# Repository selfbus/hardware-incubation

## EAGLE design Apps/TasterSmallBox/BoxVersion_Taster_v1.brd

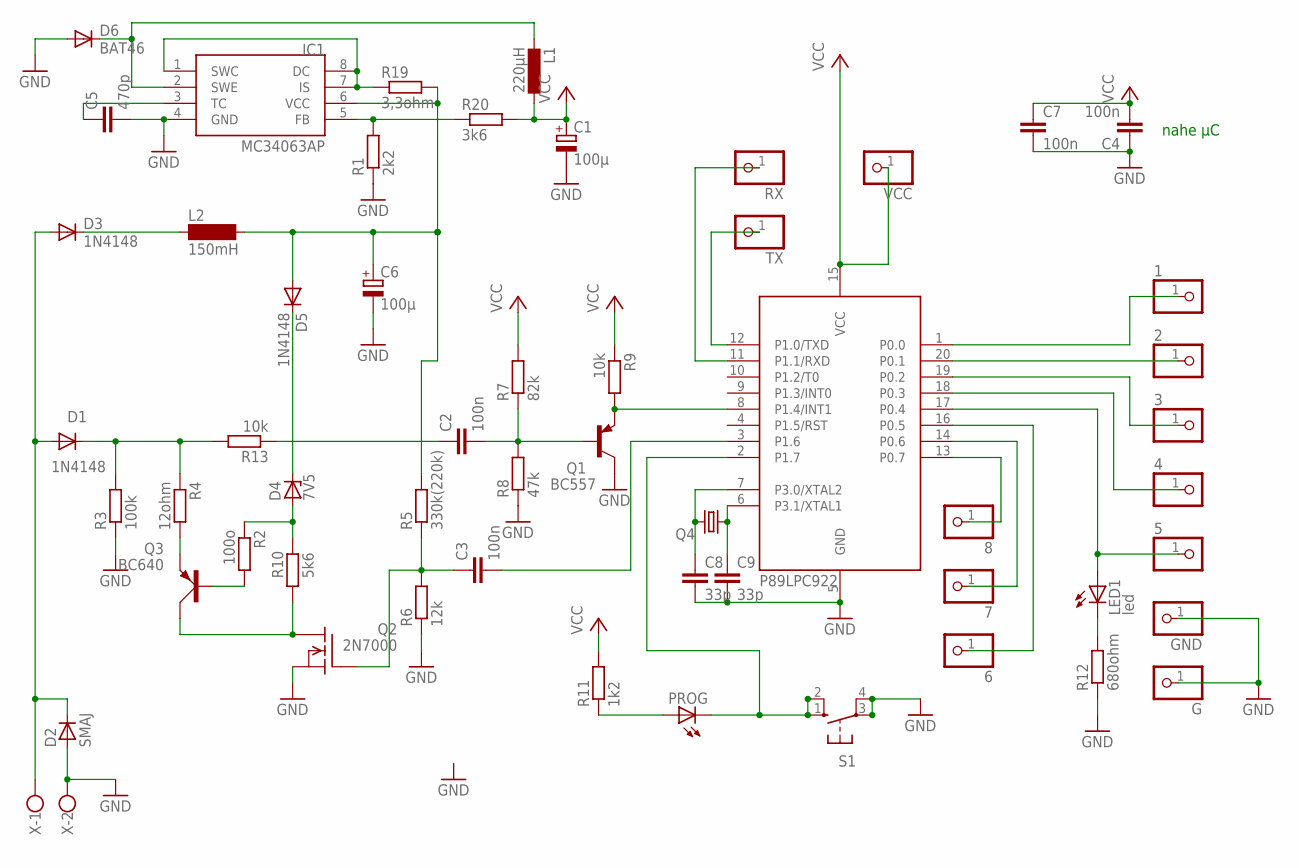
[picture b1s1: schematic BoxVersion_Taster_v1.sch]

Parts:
1, 2, 3, 4, 5, 6, 7, 8: PINHD-1X1; 1X01
C1: 100µ; E5-5
C2, C3, C4: 100n; C050-024X044
C5: 470p; C025-024X044
C6: 100µ; E5-6
C7: 100n; C1206
C8, C9: 33p; C1206
D1, D3, D5: 1N4148; D-2.5
D2: SMAJ; MELF-MLL41
D4: 7V5; ZDIO-2.5
D6: BAT46; D-2.5
G: PINHD-1X1; 1X01
GND: PINHD-1X1; 1X01
IC1: MC34063AP; DIL08
L1: 220µH; 0204/7
L2: 150mH; SD12K100
LED1: led; LZR181
PROG: LEDLZR181; LZR181
Q1: BC557; TO92
Q2: 2N7000; TO237
Q3: BC640; SOT54D
Q4: CRYSTALHC49S; HC49/S
R1: 2k2; 0207/2V
R2: 100o; 0207/2V
R3: 100k; 0207/2V
R4: 12ohm; 0207/2V
R5: 330k(220k); 0207/2V
R6: 12k; 0207/2V
R7: 82k; 0207/2V
R8: 47k; 0204/7
R9, R13: 10k; 0207/2V
R10: 5k6; 0207/2V
R11: 1k2; 0207/2V
R12: 680ohm; 0204/7
R19: 3,3ohm; 0207/2V
R20: 3k6; 0207/2V
RX: PINHD-1X1; 1X01
S1: 10-XX; B3F-10XX
TX: PINHD-1X1; 1X01
U1: 89LPC922; DIL20
VCC: PINHD-1X1; 1X01
X: W237-02P; W237-132

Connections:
GND: C1.-, C4.1, C5.2, C6.-, C7.2, C8.2, C9.2, D2.2 (A), D6.A, G.1, GND.1, IC1.4 (GND), Q1.3 (C), Q2.3 (S), R1.1, R3.1, R6.1, R8.1, R12.1, S1.3, S1.4 (P1), U1.5 (GND), X.2
unnamed: Q1.1 (E), R9.2, U1.8 (P1.4/INT1)
unnamed: C2.2, Q1.2 (B), R7.1, R8.2
unnamed: IC1.5 (FB), R1.2, R20.1
unnamed: IC1.1 (SWC), IC1.7 (IS), IC1.8 (DC), R19.1
unnamed: C3.2, U1.3 (P1.6)
unnamed: Q2.1 (D), Q3.C, R10.1
unnamed: C6.+, D5.A, IC1.6 (VCC), L2.2, R5.2, R19.2
unnamed: D3.C, L2.1
unnamed: D1.C, R3.2, R4.1, R13.2
unnamed: D6.C, IC1.2 (SWE), L1.2
unnamed: D4.A, R2.1, R10.2
unnamed: Q3.E, R4.2
unnamed: C5.1, IC1.3 (TC)
unnamed: Q3.B, R2.2
unnamed: 5.1, LED1.A, U1.17 (P0.4)
unnamed: D1.A, D2.1 (C), D3.A, X.1
unnamed: PROG.K (C), S1.1 (S), S1.2 (S1), U1.2 (P1.7)
unnamed: LED1.K (C), R12.2
unnamed: PROG.A, R11.1
unnamed: 3.1, U1.19 (P0.2)
unnamed: 1.1, U1.1 (P0.0)
unnamed: 2.1, U1.20 (P0.1)
unnamed: 4.1, U1.18 (P0.3)
unnamed: TX.1, U1.12 (P1.0/TXD)
unnamed: RX.1, U1.11 (P1.1/RXD)
unnamed: 6.1, U1.16 (P0.5)
unnamed: 8.1, U1.13 (P0.7)
unnamed: 7.1, U1.14 (P0.6)
unnamed: C9.1, Q4.1, U1.6 (P3.1/XTAL1)
unnamed: C8.1, Q4.2, U1.7 (P3.0/XTAL2)
unnamed: C2.1, R13.1
unnamed: C3.1, Q2.2 (G), R5.1, R6.2
unnamed: D4.C, D5.C
VCC: C1.+, C4.2, C7.1, L1.1, R7.2, R9.1, R11.2, R20.2, U1.15 (VCC), VCC.1

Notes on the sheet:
nahe µC
P89LPC922

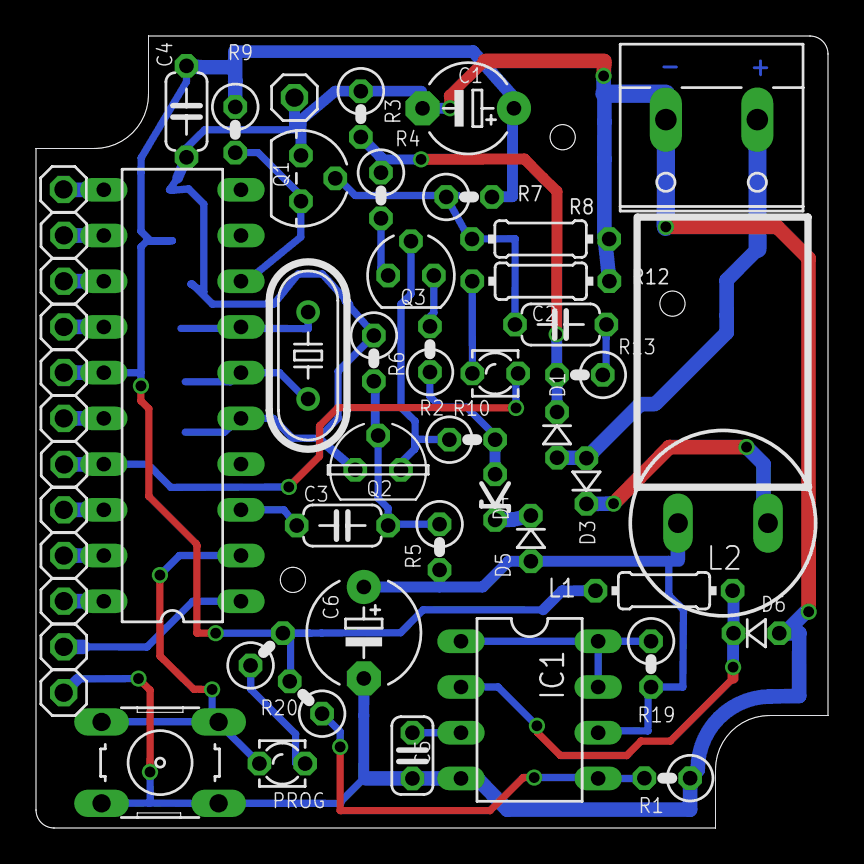
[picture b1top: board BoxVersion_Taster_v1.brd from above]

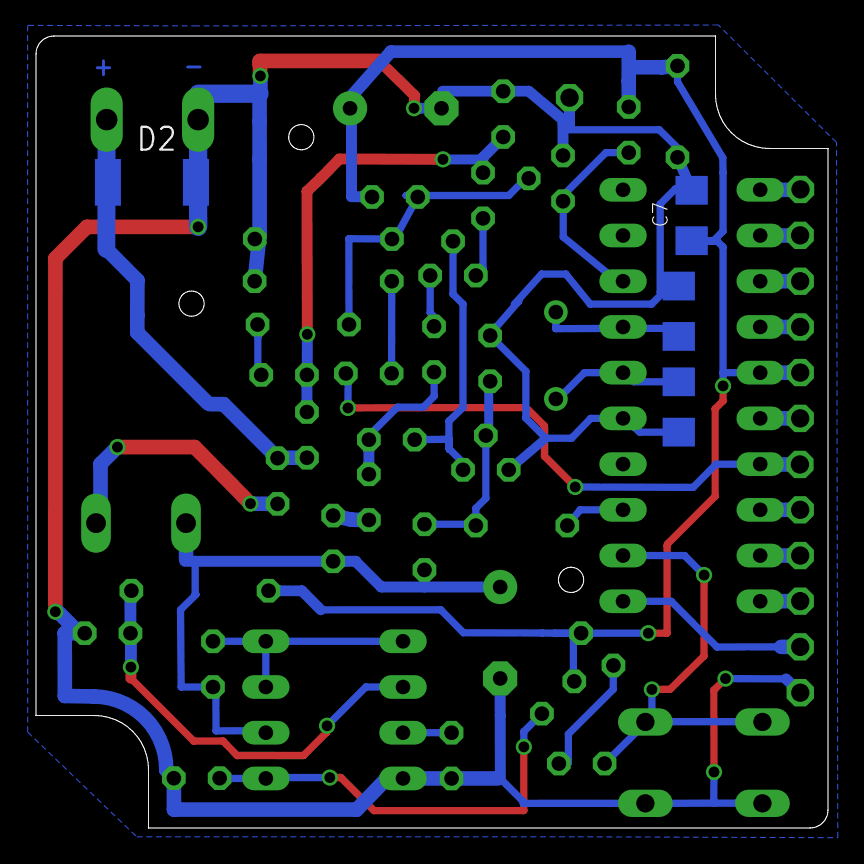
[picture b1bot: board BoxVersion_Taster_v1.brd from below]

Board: 2 copper layers, 44.0 x 44.0 mm, 56 parts (4 on the bottom side), 35 nets.

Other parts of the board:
U$1: 1551R

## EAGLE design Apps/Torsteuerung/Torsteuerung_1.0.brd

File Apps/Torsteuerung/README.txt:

Garagentor Steuerung
====================

Ziel: Ansteuerung eines Garagentor Antriebs über EIB.

Die Idee ist einen Freebus LPC Controller mit einer 8in Applikationsplatine
zu verwenden. Die Applikationsplatine wird so adaptiert dass zwei der
Eingänge als Ausgänge verwendet werden. 

Eingänge
--------

2 Endschalter Tor offen / zu
2 Motorstrom Indikatoren öffnet / schließt
1 Licht (blinkt bei Fehler)

Ausgänge
--------

Zwei Modi: entweder mit einem Ausgang alle 4 Zustände durchschalten
(Auf, Stopp, Zu, Stopp) oder mit zwei Ausgängen auf und zu ansteuern.

1 Tor auf / Tor unversal
1 Tor zu

Com Objekte
-----------

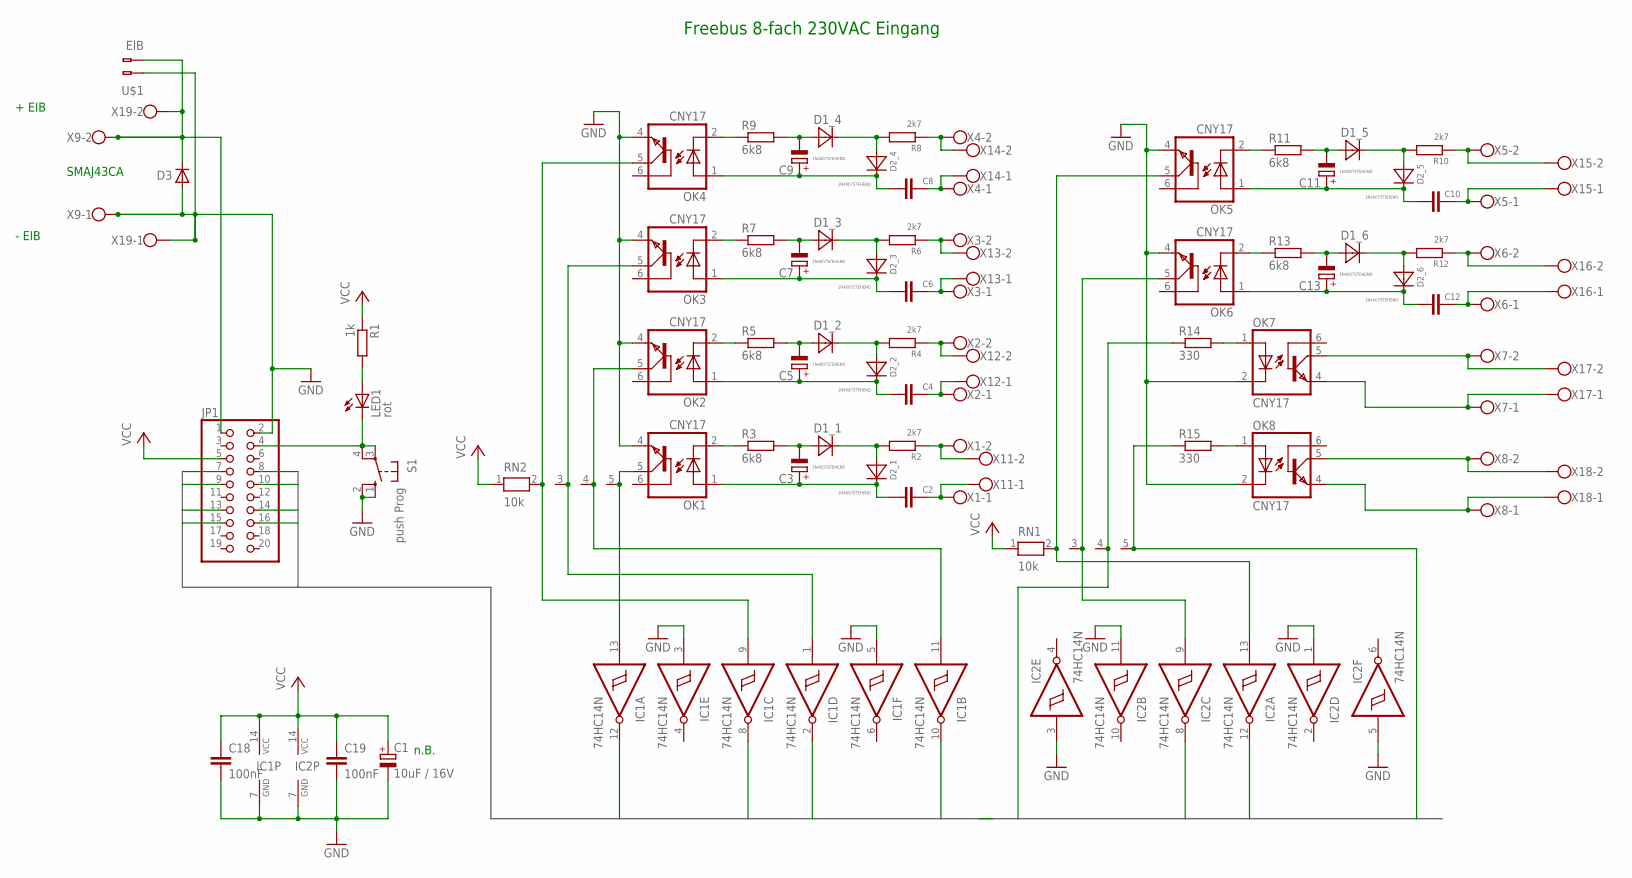
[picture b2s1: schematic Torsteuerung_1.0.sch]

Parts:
C1: 10uF / 16V; E2-4
C2, C4, C6, C8, C10, C12: C-EU075-063X106; C075-063X106
C3, C5, C7, C9, C11, C13: CPOL-EUE2-4; E2-4
C18, C19: 100nF; C050-024X044
D1_1, D1_2, D1_3, D1_4, D1_5, D1_6, D2_1, D2_2, D2_3, D2_4, D2_5, D2_6: 1N4007STEHEND; RAD2,5
D3: D-SMB; SMB
IC1, IC2: 74HC14N; DIL14
JP1: PINHD-2X10; 2X10
LED1: rot; LED3MM
OK1, OK2, OK3, OK4, OK5, OK6, OK7, OK8: CNY17; DIL06
R1: 1k; 0204/7
R2, R4, R6, R8, R10, R12: 2k7; 0207/2V
R3, R5, R7, R9, R11, R13: 6k8; 0207/2V
R14, R15: 330; 0204/5
RN1, RN2: 10k; RN-5
S1: push Prog; B3F-10XX
U$1: EIB; BUSKLEMME243-724
X1, X2, X3, X4, X5, X6, X7, X8, X9: W237-102
X11, X12, X13, X14, X15, X16, X17, X18, X19: W237-102AKL007-2P; AKL007-02

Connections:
230+_1: C2.1, C3.+, D2_1.C, OK1.1 (A)
230+_2: C4.1, C5.+, D2_2.C, OK2.1 (A)
230+_3: C6.1, C7.+, D2_3.C, OK3.1 (A)
230+_4: C8.1, C9.+, D2_4.C, OK4.1 (A)
230+_5: C10.1, C11.+, D2_5.C, OK5.1 (A)
230+_6: C12.1, C13.+, D2_6.C, OK6.1 (A)
230-_1: C3.-, D1_1.A, R3.2
230-_2: C5.-, D1_2.A, R5.2
230-_3: C7.-, D1_3.A, R7.2
230-_4: C9.-, D1_4.A, R9.2
230-_5: C11.-, D1_5.A, R11.2
230-_6: C13.-, D1_6.A, R13.2
230N_1: D1_1.C, D2_1.A, R2.2
230N_2: D1_2.C, D2_2.A, R4.2
230N_3: D1_3.C, D2_3.A, R6.2
230N_4: D1_4.C, D2_4.A, R8.2
230N_5: D1_5.C, D2_5.A, R10.2
230N_6: D1_6.C, D2_6.A, R12.2
GND: C1.-, C18.2, C19.2, D3.2 (A), IC1.3 (I), IC1.5 (I), IC1.7 (GND), IC2.1 (I), IC2.3 (I), IC2.5 (I), IC2.7 (GND), IC2.11 (I), JP1.2, OK1.4 (EMI), OK2.4 (EMI), OK3.4 (EMI), OK4.4 (EMI), OK5.4 (EMI), OK6.4 (EMI), OK7.2 (C), OK8.2 (C), S1.1 (S), S1.2 (S1), U$1.1 (B-1), X9.1, X19.1
IO1: IC1.12 (O), JP1.7
IO2: IC1.10 (O), JP1.8
IO3: IC1.2 (O), JP1.9
IO4: IC1.8 (O), JP1.10
IO5: IC2.12 (O), JP1.13
IO6: IC2.8 (O), JP1.14
IO7: JP1.15, R14.1, RN1.4
IO8: JP1.16, R15.1, RN1.5
unnamed: C8.2, X4.1, X14.1
unnamed: R8.1, X4.2, X14.2
unnamed: C6.2, X3.1, X13.1
unnamed: R6.1, X3.2, X13.2
unnamed: C4.2, X2.1, X12.1
unnamed: R4.1, X2.2, X12.2
unnamed: C2.2, X1.1, X11.1
unnamed: R2.1, X1.2, X11.2
unnamed: R12.1, X6.2, X16.2
unnamed: C12.2, X6.1, X16.1
unnamed: OK7.5 (COL), X7.2, X17.2
unnamed: OK8.4 (EMI), X8.1, X18.1
unnamed: R10.1, X5.2, X15.2
unnamed: C10.2, X5.1, X15.1
unnamed: OK7.4 (EMI), X7.1, X17.1
unnamed: OK8.5 (COL), X8.2, X18.2
unnamed: IC2.13 (I), OK5.5 (COL), RN1.2
unnamed: IC2.9 (I), OK6.5 (COL), RN1.3
unnamed: D3.1 (C), JP1.1, U$1.2 (B-2), X9.2, X19.2
unnamed: OK8.1 (A), R15.2
unnamed: OK7.1 (A), R14.2
unnamed: IC1.13 (I), OK1.5 (COL), RN2.5
unnamed: IC1.11 (I), OK2.5 (COL), RN2.4
unnamed: JP1.4, LED1.K (C), S1.3, S1.4 (P1)
unnamed: LED1.A, R1.2
unnamed: IC1.1 (I), OK3.5 (COL), RN2.3
unnamed: IC1.9 (I), OK4.5 (COL), RN2.2
OPT_1: OK1.2 (C), R3.1
OPT_2: OK2.2 (C), R5.1
OPT_3: OK3.2 (C), R7.1
OPT_4: OK4.2 (C), R9.1
OPT_5: OK5.2 (C), R11.1
OPT_6: OK6.2 (C), R13.1
VCC: C1.+, C18.1, C19.1, IC1.14 (VCC), IC2.14 (VCC), JP1.5, R1.1, RN1.1, RN2.1

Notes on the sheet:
+ EIB
- EIB
Freebus 8-fach 230VAC Eingang
SMAJ43CA
n.B.

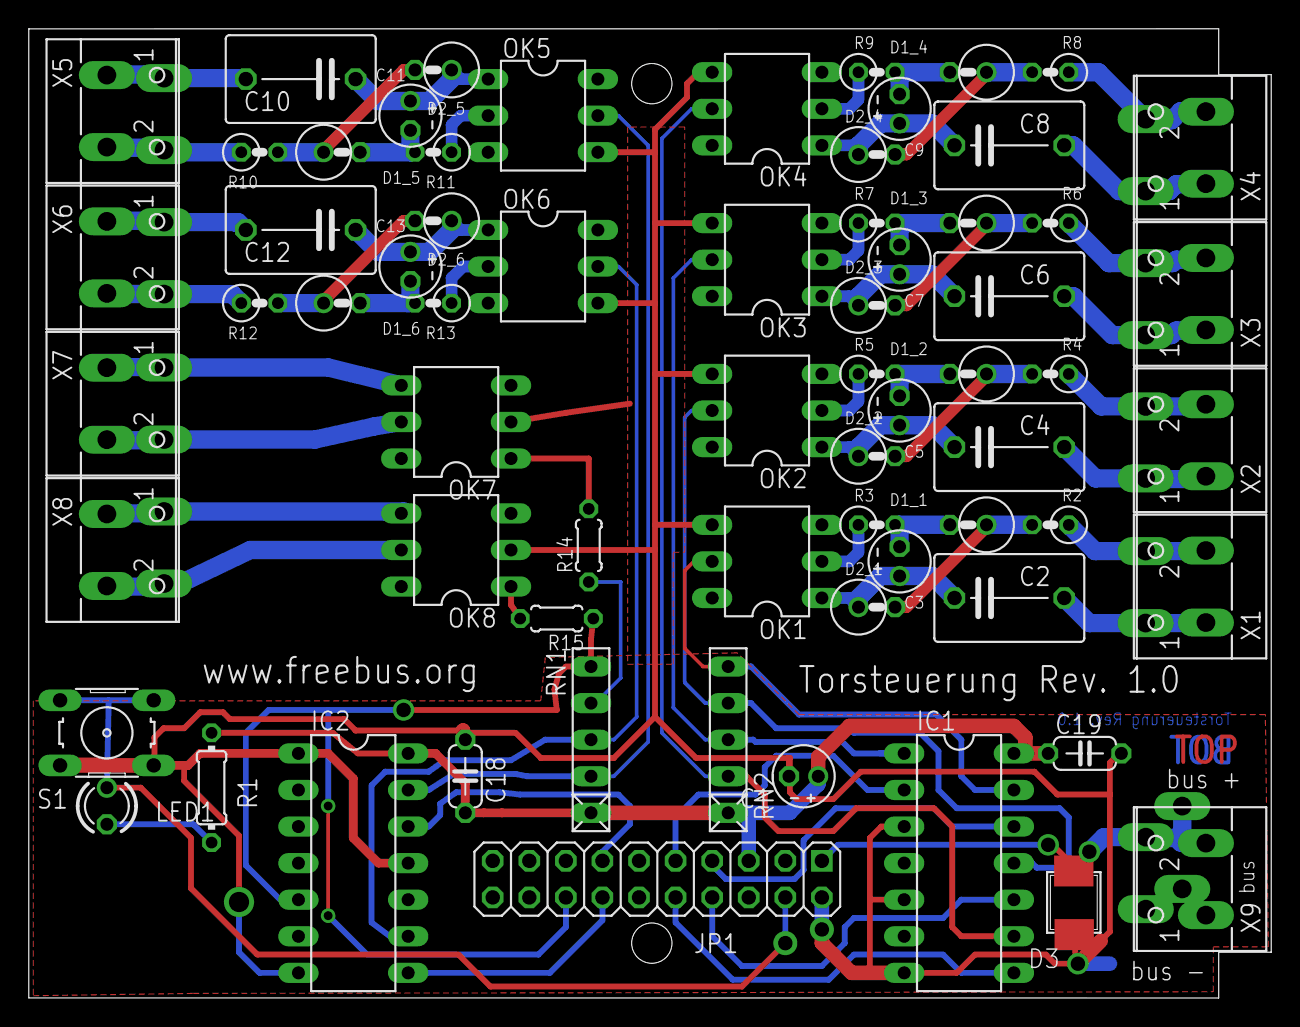
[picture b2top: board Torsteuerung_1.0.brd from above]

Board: 2 copper layers, 86.3 x 67.3 mm, 77 parts (0 on the bottom side), 61 nets.

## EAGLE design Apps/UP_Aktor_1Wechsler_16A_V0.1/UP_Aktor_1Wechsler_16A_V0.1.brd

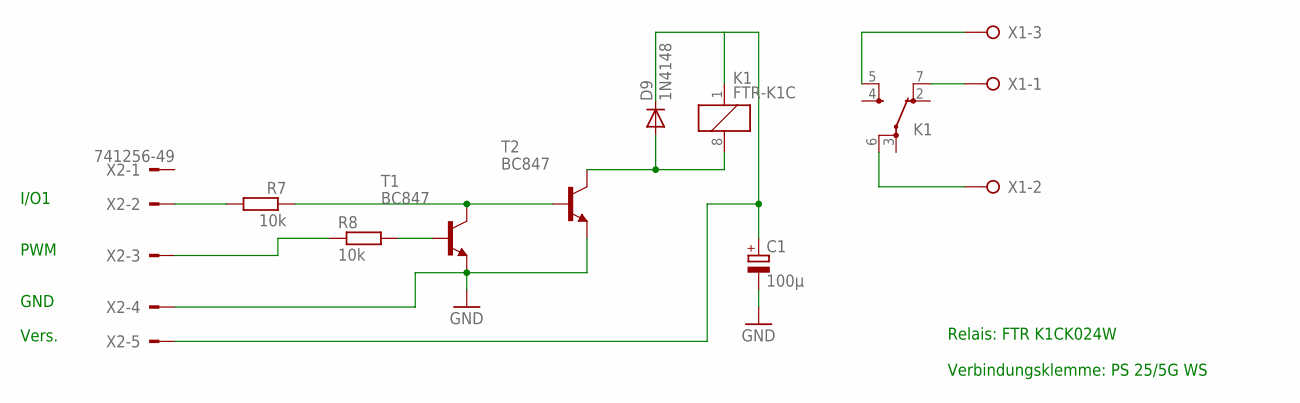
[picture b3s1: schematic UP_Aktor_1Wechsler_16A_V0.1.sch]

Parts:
C1: 100µ; E3,5-8
D9: 1N4148; MINIMELF
K1: FTR-K1C
R7, R8: 10k; M1206
T1, T2: BC847; SOT23
X1: W237-03P; W237-133
X2: 741256-49

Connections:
GND: C1.-, T1.2 (E), T2.2 (E), X2.4
IO2: R7.2, X2.2
unnamed: K1.5 (SB), X1.3
unnamed: K1.7 (OB), X1.1
unnamed: K1.6 (PB), X1.2
unnamed: R8.1, X2.3
unnamed: R7.1, T1.3 (C), T2.1 (B)
unnamed: R8.2, T1.1 (B)
R3: D9.A, K1.8 (2), T2.3 (C)
VDD_IN: C1.+, D9.C, K1.1, X2.5

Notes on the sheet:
PWM
I/O1
Vers.
GND
Relais: FTR K1CK024W Verbindungsklemme: PS 25/5G WS

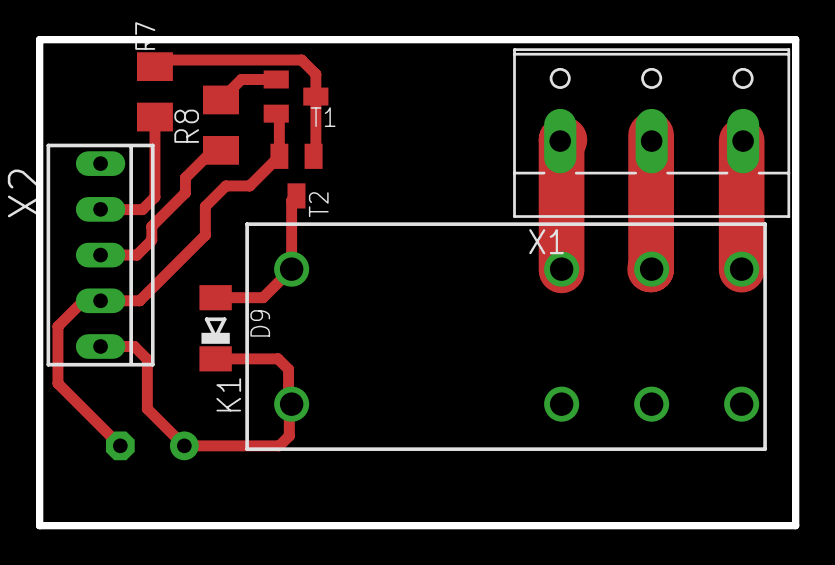
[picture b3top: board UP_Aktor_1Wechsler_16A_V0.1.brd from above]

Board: 2 copper layers, 42.0 x 27.0 mm, 9 parts (1 on the bottom side), 10 nets.

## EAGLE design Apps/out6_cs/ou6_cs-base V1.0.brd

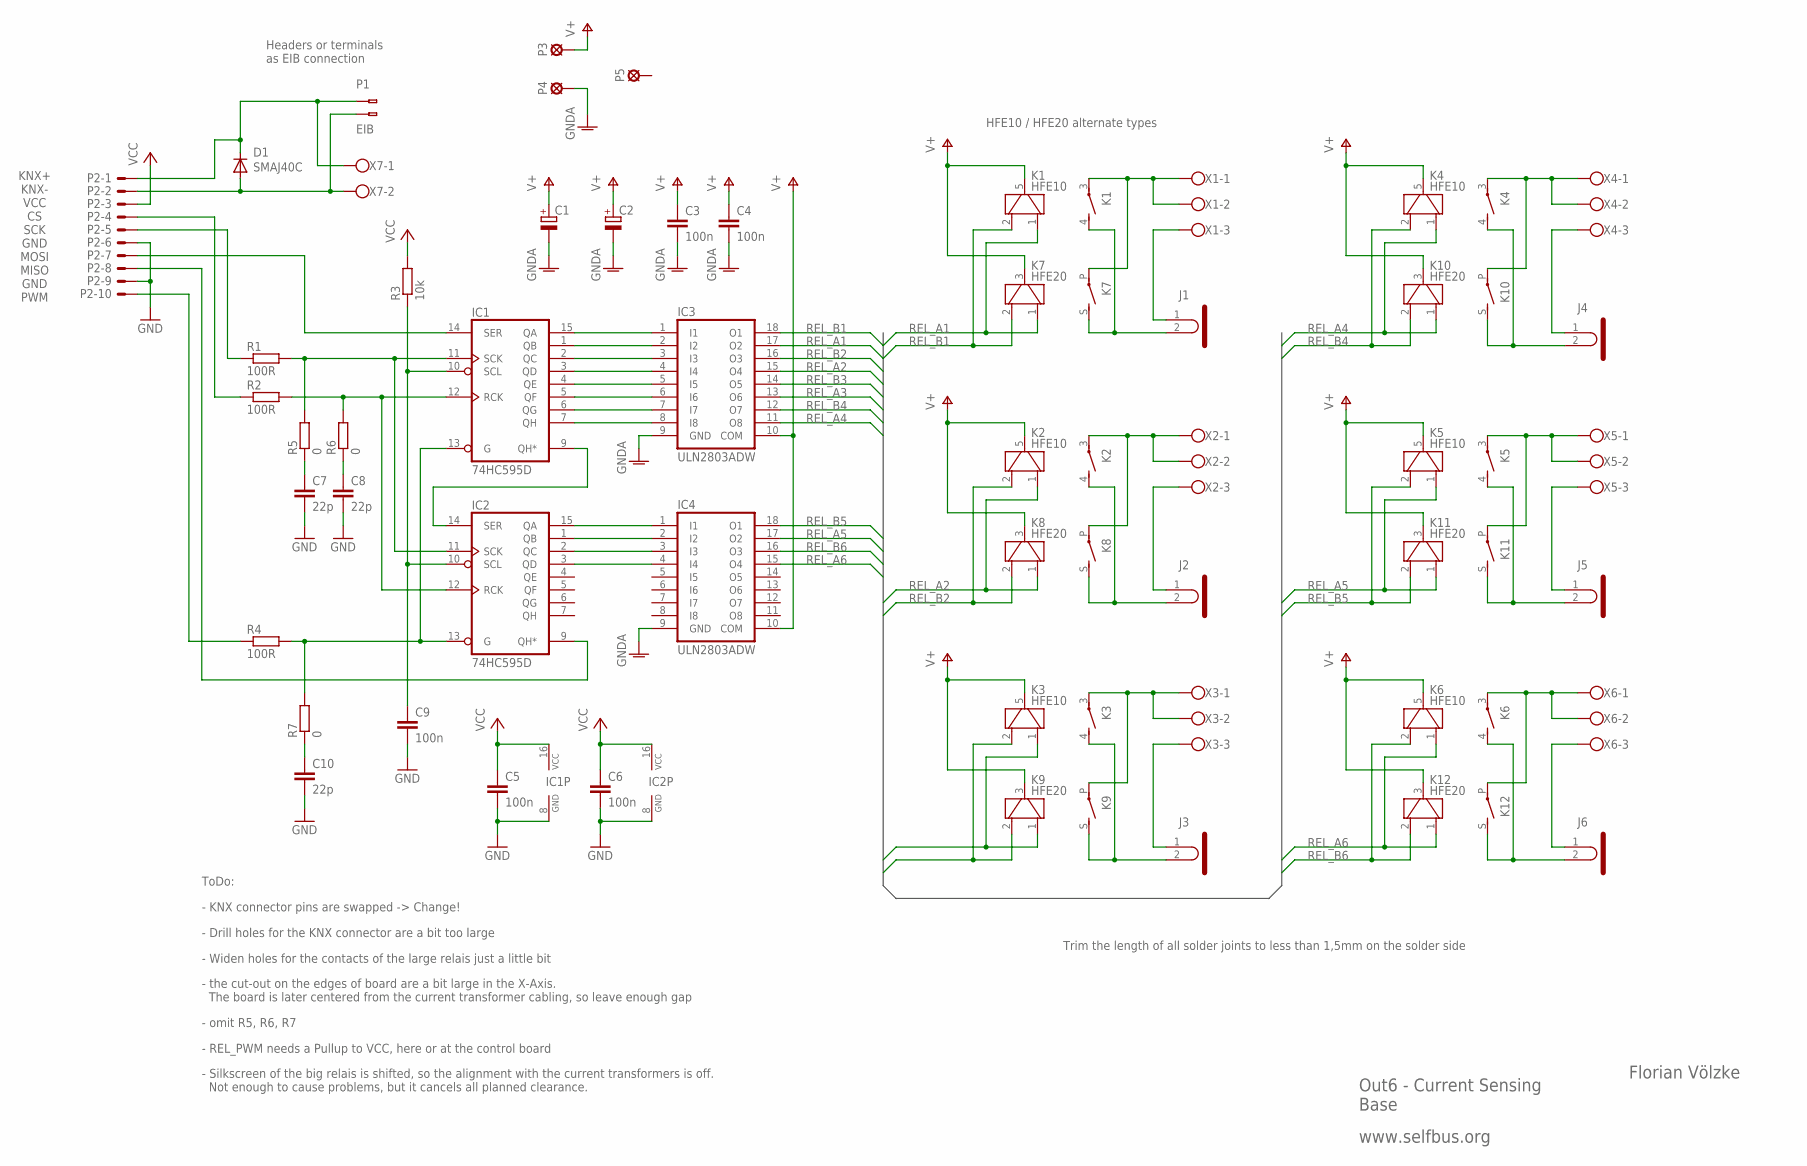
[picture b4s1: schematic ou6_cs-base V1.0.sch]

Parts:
C1: CPOL-EUE5-13-20; E5-13-20
C2: CPOL-EUE5-13-20R; E5-13-20R
C3, C4, C5, C6, C9: 100n; R0805M
C7, C8, C10: 22p; R0805M
D1: SMAJ40C; SMB
IC1, IC2: 74HC595D; SO16
IC3, IC4: ULN2803ADW; SO18W
J1, J2, J3, J4, J5, J6: IXFORMER_PRIMONLY; IXFORMERANTIPART
K1, K2, K3, K4, K5, K6: HFE10; PCB_REL_BIG_POWER_NO
K7, K8, K9, K10, K11, K12: HFE20; PCB_REL_HP_NO_SNGLPIN
P1: EIB; BUSKLEMME243-724
P2: ML10E; ML10
P3, P4, P5: SE1.5; SE15
R1, R2, R4: 100R; R0805M
R3: 10k; R0805M
R5, R6, R7: 0; R0805M
X1, X2, X3, X4, X5, X6: KLEMME3POL5_08
X7: KLEMME2POL5_08

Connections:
GND: C5.2, C6.2, C7.2, C8.2, C9.2, C10.2, IC1.8 (GND), IC2.8 (GND), P2.6, P2.9
GNDA: C1.-, C2.-, C3.2, C4.2, IC3.9 (GND), IC4.9 (GND), P4.MP
unnamed: IC1.9 (QH*), IC2.14 (SER)
unnamed: IC1.11 (SCK), IC2.11 (SCK), R1.2, R5.2
unnamed: IC1.12 (RCK), IC2.12 (RCK), R2.2, R6.2
unnamed: IC1.14 (SER), P2.7
unnamed: IC1.13 (G), IC2.13 (G), R4.2, R7.2
unnamed: K2.3, K8.P, X2.P$1, X2.P$2
unnamed: J3.2, K3.4 (S), K9.S
unnamed: J2.2, K2.4 (S), K8.S
unnamed: J1.2, K1.4 (S), K7.S
unnamed: J2.1, X2.P$3
unnamed: J1.1, X1.P$3
unnamed: K1.3, K7.P, X1.P$1, X1.P$2
unnamed: IC2.9 (QH*), P2.8
unnamed: K3.3, K9.P, X3.P$1, X3.P$2
unnamed: K4.3, K10.P, X4.P$1, X4.P$2
unnamed: J3.1, X3.P$3
unnamed: IC1.15 (QA), IC3.1 (I1)
unnamed: K5.3, K11.P, X5.P$1, X5.P$2
unnamed: IC1.1 (QB), IC3.2 (I2)
unnamed: K6.3, K12.P, X6.P$1, X6.P$2
unnamed: IC1.2 (QC), IC3.3 (I3)
unnamed: J6.1, X6.P$3
unnamed: J6.2, K6.4 (S), K12.S
unnamed: J5.2, K5.4 (S), K11.S
unnamed: J4.2, K4.4 (S), K10.S
unnamed: IC1.3 (QD), IC3.4 (I4)
unnamed: IC1.4 (QE), IC3.5 (I5)
unnamed: IC1.5 (QF), IC3.6 (I6)
unnamed: IC1.6 (QG), IC3.7 (I7)
unnamed: J5.1, X5.P$3
unnamed: IC1.7 (QH), IC3.8 (I8)
unnamed: IC2.15 (QA), IC4.1 (I1)
unnamed: J4.1, X4.P$3
unnamed: IC2.1 (QB), IC4.2 (I2)
unnamed: IC2.2 (QC), IC4.3 (I3)
unnamed: IC2.3 (QD), IC4.4 (I4)
unnamed: C9.1, IC1.10 (SCL), IC2.10 (SCL), R3.1
unnamed: P2.5, R1.1
unnamed: P2.4, R2.1
unnamed: D1.1 (C), P1.1 (B-1), P2.1, X7.P$1
unnamed: P2.10, R4.1
unnamed: D1.2 (A), P1.2 (B-2), P2.2, X7.P$2
unnamed: C7.1, R5.1
unnamed: C8.1, R6.1
unnamed: C10.1, R7.1
REL_A1: IC3.17 (O2), K1.1 (3), K7.1 (3)
REL_A2: IC3.15 (O4), K2.1 (3), K8.1 (3)
REL_A3: IC3.13 (O6), K3.1 (3), K9.1 (3)
REL_A4: IC3.11 (O8), K4.1 (3), K10.1 (3)
REL_A5: IC4.17 (O2), K5.1 (3), K11.1 (3)
REL_A6: IC4.15 (O4), K6.1 (3), K12.1 (3)
REL_B1: IC3.18 (O1), K1.2, K7.2
REL_B2: IC3.16 (O3), K2.2, K8.2
REL_B3: IC3.14 (O5), K3.2, K9.2
REL_B4: IC3.12 (O7), K4.2, K10.2
REL_B5: IC4.18 (O1), K5.2, K11.2
REL_B6: IC4.16 (O3), K6.2, K12.2
V+: C1.+, C2.+, C3.1, C4.1, IC3.10 (COM), IC4.10 (COM), K1.5 (1), K2.5 (1), K3.5 (1), K4.5 (1), K5.5 (1), K6.5 (1), K7.3 (1), K8.3 (1), K9.3 (1), K10.3 (1), K11.3 (1), K12.3 (1), P3.MP
VCC: C5.1, C6.1, IC1.16 (VCC), IC2.16 (VCC), P2.3, R3.2

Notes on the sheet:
KNX+ KNX- VCC CS SCK GND MOSI MISO GND PWM
Florian Völzke
Out6 - Current Sensing Base
www.selfbus.org
HFE10 / HFE20 alternate types
Headers or terminals as EIB connection
ToDo:
- KNX connector pins are swapped -> Change!
- Drill holes for the KNX connector are a bit too large
- Widen holes for the contacts of the large relais just a little bit
Trim the length of all solder joints to less than 1,5mm on the solder side
- the cut-out on the edges of board are a bit large in the X-Axis. The board is later centered from the current transformer cabling, so leave enough gap
- omit R5, R6, R7
- REL_PWM needs a Pullup to VCC, here or at the control board
- Silkscreen of the big relais is shifted, so the alignment with the current transformers is off. Not enough to cause problems, but it cancels all planned clearance.

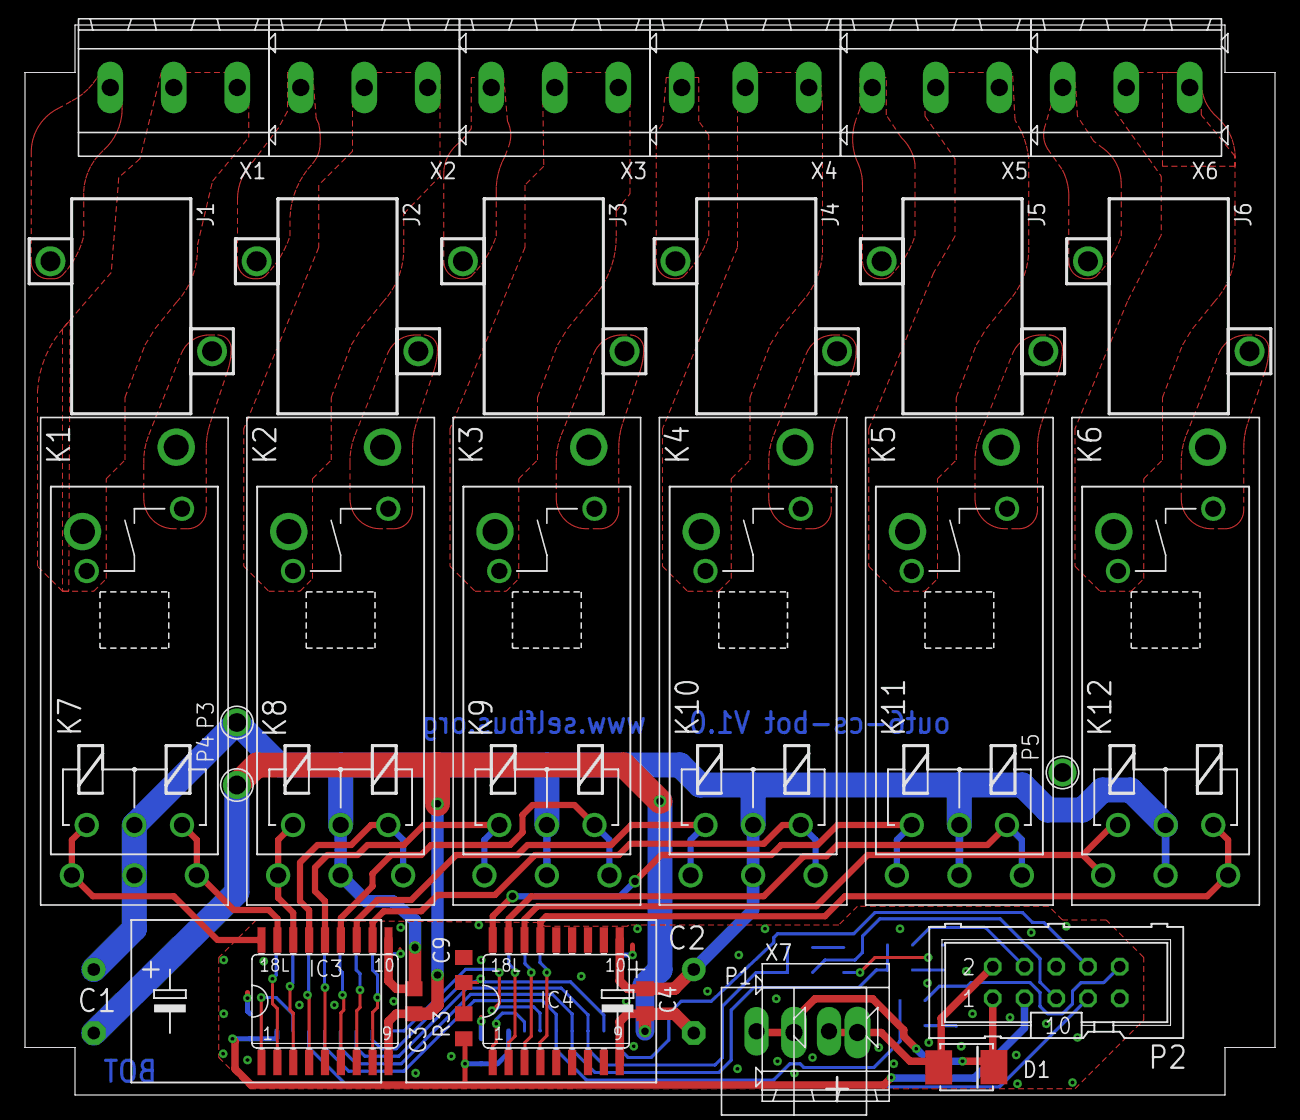
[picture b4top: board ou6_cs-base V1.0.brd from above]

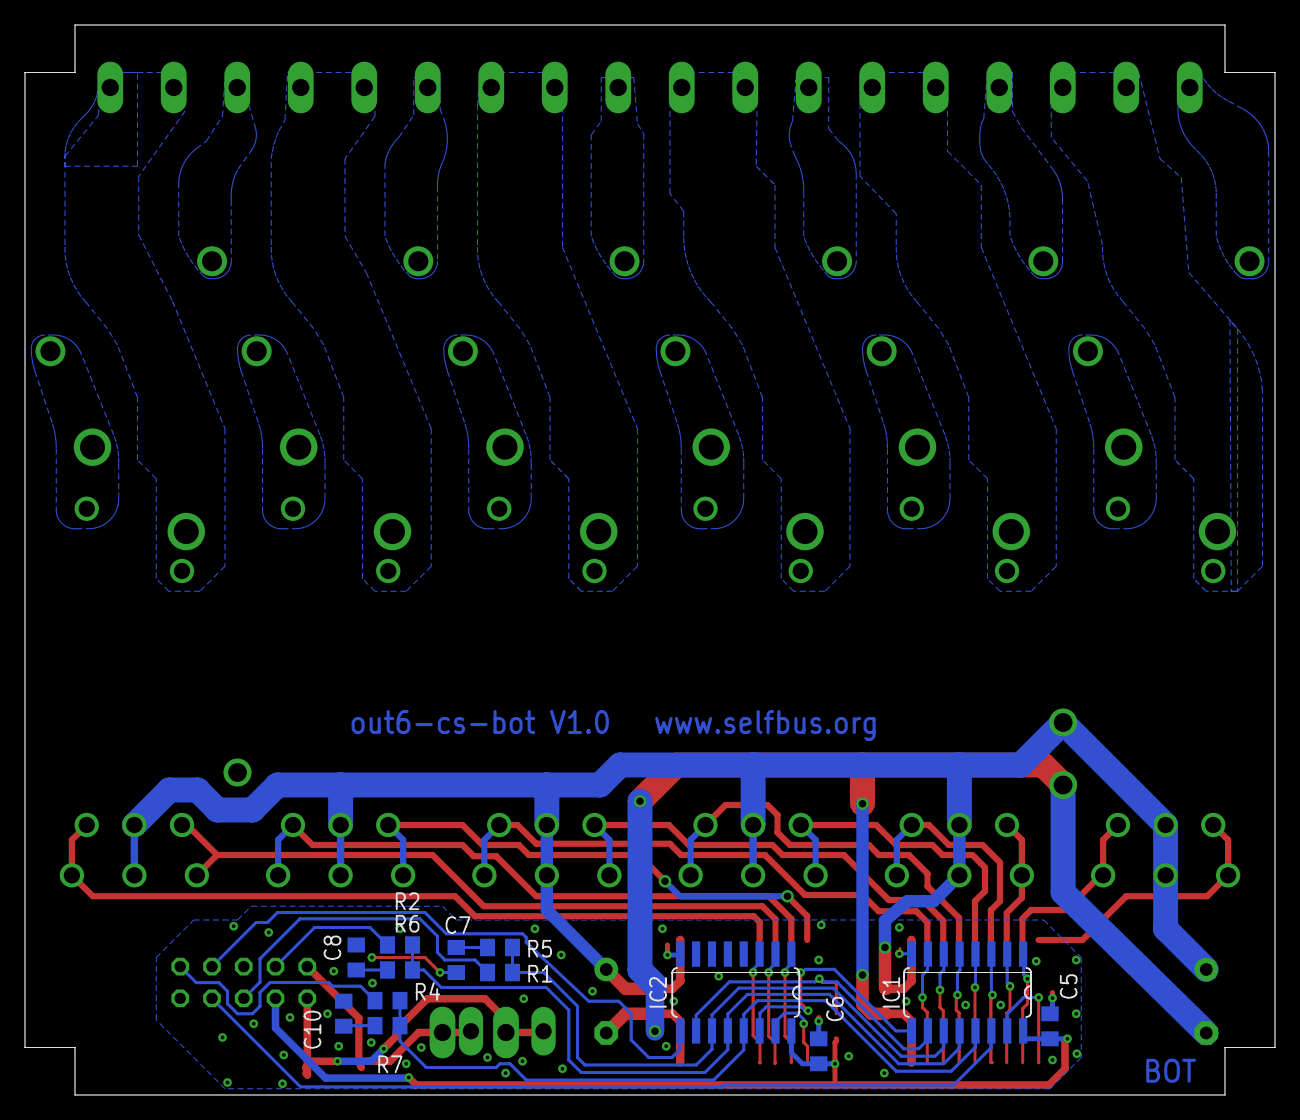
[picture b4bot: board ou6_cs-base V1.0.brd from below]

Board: 2 copper layers, 100.0 x 85.6 mm, 52 parts (13 on the bottom side), 61 nets.

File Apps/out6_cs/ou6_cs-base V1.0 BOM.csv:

"Qty","Value","Package","Parts","Anmerkung","Lieferant","Bestellartikel","Artikelpreis","VPE","Postenpreis"
1,,"Platine out6-cs-base",,,,,,,
1,,"Gehäuse",,,"Reichelt","HUT 6-C","5,9",1,"5,9"
1,,,"EIB-Steckeraufnahme","3D-Druck (wenn Einlötstifte P1 verwendet)",,,,,
2,,"Elko radial D12,5mm H20mm","C1, C2","Evtl passt auch RAD 1.000/35, mir wurden kürzere als in den technischen Daten geliefert","Reichelt","RAD FR 1.000/35","0,65",1,"1,3"
6,,"64mm PVC-Aderleitung 1,5mm² H07V-U","J1, J2, J3, J4, J5, J6","beidseitig je 6mm abisolieren","Reichelt","H07VU 1,5-25 SW","6,35",390,"0,0976923077"
6,,"52mm Isolierschlauch Innen-D 3mm","J1, J2, J3, J4, J5, J6","Alternativartikel: 541594, 549957","Conrad",540836,"0,6",19,"0,1894736842"
3,,"42mm Draht 1,0 bis 1,3mm Durchmesser",,"zur Fixierung der Ctrl-Platine auf der Base-Platine",,,,,
1,,"KLEMME2POL5_08","X7","Oder P1 bestücken (Einlötstifte)","Oldis Shop","Anschlußklemme 2 polig","0,32",1,"0,32"
6,,"KLEMME3POL5_08","X1, X2, X3, X4, X5, X6",,"Oldis Shop","Anschlußklemme 3polig","0,48",1,"2,88"
1,,"Wannenstecker 2x5pol 2,54mm","P2",,"Reichelt","WSL 10G","0,09",1,"0,09"
1,,"Pfostenbuchse 2x5pol 2,54mm",,,"Reichelt","PFL 10","0,09",1,"0,09"
3,"22p","C0805","C7, C8, C10","CAPACITOR, European symbol","Reichelt","NPO-G0805 22P","0,04",1,"0,12"
3,0,"R0805","R5, R6, R7","RESISTOR, European symbol","Reichelt","SMD-0805 0,00","0,03",1,"0,09"
3,"100R","R0805","R1, R2, R4","RESISTOR, European symbol","Reichelt","SMD-0805 100","0,03",1,"0,09"
5,"100n","C0805","C3, C4, C5, C6, C9","CAPACITOR, European symbol","Reichelt","X7R-G0805 100N","0,04",1,"0,2"
1,"10k","R0805","R3","RESISTOR, European symbol","Reichelt","SMD-0805 10,0K","0,03",1,"0,03"
2,"74HC595D",,"IC1, IC2","8-bit SHIFT REGISTER, output latch","Reichelt","SMD HC 595","0,2",1,"0,4"
2,"EIB","Einlötstifte für die EIB-Busklemme","P1","17,5mm lange, 1mm dicke Einlötstifte (oder X7 bestücken)","Conrad",1226206,"3,1",100,"0,062"
3,"SE1.5","42mm PVC-Aderleitung 1,5mm² H07V-U","P3, P4, P5",,"Reichelt","H07VU 1,5-25 SW","6,35",595,"0,0320168067"
1,"SMAJ40CA","SMB","D1","DIODE","Oldis Shop","SMAJ 40 AC Überspannungsdiode","0,2",1,"0,2"
2,"ULN2803ADW","SO18W","IC3, IC4","DRIVER ARRAY","Reichelt","ULN 2803 D","0,4",1,"0,8"
6,"HFE10","Hong-Fa HFE10-2-12-HT-L2","K1, K2, K3, K4, K5, K6","oder das HFE20 (weniger Ansteuerleistung)","Aliexpress","HFE10-2-12-HT-L2",4,1,24
6,"HFE20","Hong-Fa HFE20-1-012-1HD","K7, K8, K9, K10, K11, K12","oder das HFE10 (mehr Schaltvermögen)","Reichelt","HFE20-1-012-1HD","6,65",1,"39,9"
